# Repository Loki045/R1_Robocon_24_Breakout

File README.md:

# R1_Robocon_24_Breakout
Breakout and control interface PCB designed for Robocon 2024 R1 robot, supporting Arduino Mega + Host Shield stacking, motor control interfaces, and regulated power distribution from external supply modules.

# Robocon 2024 – R1 Control Breakout PCB

This repository contains the hardware design files for the **R1 Control Breakout PCB** used in the Robocon 2024 robot.

The board was designed to serve as a **stackable control and interface breakout**, enabling easy connection of motors, actuators, and control modules using an **Arduino Mega + Host Shield** stack.

---

## 📌 Robot Task Overview

In Robocon 2024, **Robot 1 (R1)** performed the following operations:

- Navigated across Area 1
- Picked up seedlings
- Placed up to **12 seedlings** into assigned circular positions
- Moved to Area 2
- Threw balls in alternating sequence:
  - Team-colored ball (Red/Blue)
  - Violet ball
  - Repeat sequence
- Threw balls toward Area 3 based on number of successfully placed seedlings

This PCB supported the control and actuator interfacing required to perform these tasks.

---

## ⚙️ Board Overview

The R1 PCB was designed as a **centralized control breakout board**, allowing:

- Direct mounting of **Arduino Mega**
- Stacking of **USB Host Shield**
- Organized connection of motors and actuators
- Easy access to multiple communication pins
- Distribution of regulated voltages received from an **external power distribution board**

This modular approach simplified robot wiring and improved system maintainability.

---

## 🔧 Key Features

- Arduino Mega compatible stacking layout
- USB Host Shield support (for controller interface)
- 4 PWM motor connectors for locomotion control
- Servo motor connectors
- Stepper motor connectors
- BLDC motor interface connectors
- Kill switch interface
- External indicating lamp connectors
- Extra UART headers
- Additional GPIO expansion pins
- LED power/status indicators
- Decoupling capacitors for stable operation

---

## 🔌 Power Interface

Regulated voltages were supplied from an **external power distribution board**.

### Input Power (via Screw Terminals):

- 12V Input
- 7.4V Input
- 5V Input

### On-board Power Headers:

- 7.4V Output Headers
- 5V Output Headers
- GND Headers

These headers enabled clean routing of regulated voltages to connected modules.

---

## 🎮 Motor & Actuator Interfaces

### Locomotion Control:

- 4 PWM output connectors for Cytron Smart Drive Mdds30 Dual 30A motor driver

### Actuator Support:

- Multiple Servo connectors
- Stepper motor connectors
- BLDC motor interface connectors

These supported the mechanisms required for seedling placement and ball throwing operations.

---

## 🧩 Additional Interfaces

- Kill Switch Connector
- External Indicator Lamp Connectors
- Extra UART Communication Headers
- General-Purpose GPIO Expansion Pins
- LED Indicators for Power/Status Monitoring

---

## 🧰 Hardware Stack

Designed to support:

- Arduino Mega 2560 (Main Controller)
- USB Host Shield
- Redgear Controller (via Host Shield)

This stack allowed wireless/manual control of the robot.

---

## 📂 Repository Contents

R1_PCB_2024-25_VRC/

    ├── PCB Layout File
    ├── Project File
    ├── Schematic File 
Images/

    ├── Top Layer View  
    ├── Bottom Layer View  
    ├── 3D View  
      
.gitignore

README.md

---

## 🛠 Tools Used

- KiCad — Schematic and PCB Design
- Arduino IDE — Firmware Development

---

## 🎯 Application

This PCB was used in the **Robocon 2024 R1 robot**, providing structured connectivity for locomotion motors, actuators, and control interfaces required for seedling placement and ball-throwing operations.

---

## 👨‍💻 Contribution

Developed as part of the Robocon 2024 electronics system, contributing to hardware layout planning, connector design, and system-level integration for robot subsystems.

---

## 📸 PCB Images

- Schematic

- F.Cu Layer View

- B.Cu Layer View

- 3D View

---

## 📎 Design Intent

This board was designed to reduce wiring complexity, improve modularity, and enable rapid maintenance during robot testing and competition.

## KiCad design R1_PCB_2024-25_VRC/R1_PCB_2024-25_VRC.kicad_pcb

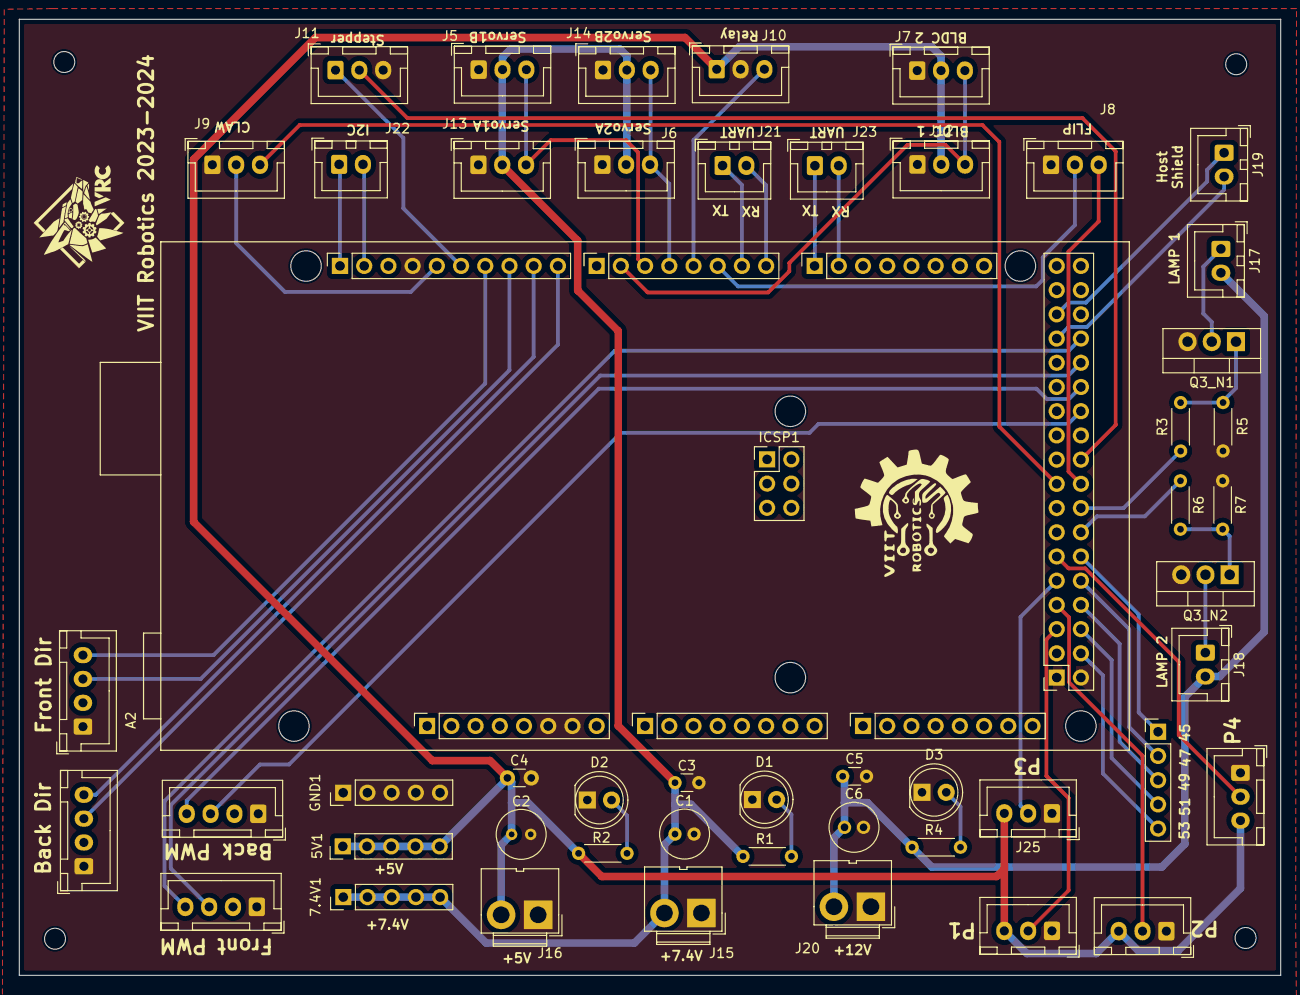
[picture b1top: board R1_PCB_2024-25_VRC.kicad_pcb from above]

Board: 2 copper layers, 132.3 x 100.3 mm, 64 parts (1 on the bottom side), 48 nets.

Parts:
5V1, 7.4V1: Conn_01x05; PinHeader_1x05_P2.54mm_Vertical
., .#2: .; logo
A2: ARDUINO_MEGA_2560_REV3_A000067; ARDUINO_ARDUINO_MEGA_2560_REV3_A000067
C1: 10 mf; C_Radial_D5.0mm_H7.0mm_P2.00mm
C2, C6: 100 nf; C_Radial_D5.0mm_H7.0mm_P2.00mm
C3, C4, C5: 0.1uF; C_Disc_D3.0mm_W1.6mm_P2.50mm
D1, D2, D3: LED; LED_D5.0mm
DIR1: Conn_01x05; PinHeader_1x05_P2.54mm_Vertical
GND1: Conn_01x05; PinHeader_1x05_P2.54mm_Vertical
H1, H2, H3, H4: MountingHole; MountingHole_2.2mm_M2
ICSP1: Conn_02x03_Odd_Even; PinHeader_2x03_P2.54mm_Vertical
J1, J2#2: FRONT; JST_XH_B4B-XH-A_1x04_P2.50mm_Vertical
J1#2: Power; PinSocket_1x08_P2.54mm_Vertical
J2: PWM; PinSocket_1x10_P2.54mm_Vertical
J3, J4#2: BACK; JST_XH_B4B-XH-A_1x04_P2.50mm_Vertical
J3#2, J5: Analog; PinSocket_1x08_P2.54mm_Vertical
J4: PWM; PinSocket_1x08_P2.54mm_Vertical
J5#2, J6#2, J7#2, J8, J9, J10, J11, J12, J13, J14, J24, J25, J26, J27: Conn_01x03; JST_XH_B3B-XH-A_1x03_P2.50mm_Vertical
J6: Communication; PinSocket_1x08_P2.54mm_Vertical
J7: Digital; PinSocket_2x18_P2.54mm_Vertical
J15, J16, J20: Conn_01x02; JWT_A3963_1x02_P3.96mm_Vertical
J17, J18, J19, J21, J22, J23: Conn_01x02; JST_XH_B2B-XH-A_1x02_P2.50mm_Vertical
Q3_N1, Q3_N2: IRF3205; TO-220-3_Vertical
R1, R4: 360; R_Axial_DIN0204_L3.6mm_D1.6mm_P5.08mm_Horizontal
R2: 220; R_Axial_DIN0204_L3.6mm_D1.6mm_P5.08mm_Horizontal
R3, R5, R6, R7: R; R_Axial_DIN0204_L3.6mm_D1.6mm_P5.08mm_Horizontal

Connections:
45: A2.45, DIR1.1, J7.12
47: A2.47, DIR1.2, J7.10
49: A2.49, DIR1.3, J7.8
51: A2.51, DIR1.4, J7.6
53: A2.53, DIR1.5, J7.4
+5V: 5V1.1, 5V1.2, 5V1.3, 5V1.4, 5V1.5, C2.1, C4.1, J7.35, J7.36, J7#2.2, J10.1, J12.2, J16.2, J24.3, J25.3, J26.3, J27.3, R2.2
+7.4V: 7.4V1.1, 7.4V1.2, 7.4V1.3, 7.4V1.4, 7.4V1.5, C1.1, C3.1, J5#2.2, J6#2.2, J13.2, J14.2, J15.2, R1.2
+12V: C5.1, C6.1, J17.2, J18.2, J20.2, R4.2
BL_AN1: A2.8, J2.10, J3.3
BL_IN1: A2.33, J4#2.3, J7.21
BR_AN2: A2.9, J2.9, J3.4
BR_IN2: A2.31, J4#2.4, J7.23
CLAW_DIR: A2.38, J7.17, J9.3
CLAW_PWM: A2.13, J2.5, J9.2
ESC_PWM: A2.6, J4.2, J7#2.3, J12.3
FLIP_DIR: A2.39, J7.18, J8.3
FLIP_PWM: A2.2, J4.6, J8.2
FL_AN1: A2.10, J1.3, J2.8
FL_IN1: A2.29, J2#2.3, J7.25
FR_AN2: A2.11, J1.4, J2.7
FR_IN2: A2.27, J2#2.4, J7.27
GND: A2.GND1, A2.GND2, A2.GND3, A2.GND4, A2.GND5, C1.2, C2.2, C3.2, C4.2, C5.2, C6.2, D1.1 (K), D2.1 (K), D3.1 (K), GND1.1, GND1.2, GND1.3, GND1.4, GND1.5, J1.1, J1#2.6, J1#2.7, J2.4, J2#2.1, J3.1, J4#2.1, J5#2.1, J6#2.1, J7.1, J7.2, J7#2.1, J8.1, J9.1, J10.2, J11.3, J12.1, J13.1, J14.1, J15.1, J16.1, J20.1, J24.1, J25.1, J26.1, J27.1, Q3_N1.3 (S), Q3_N2.3 (S), R5.1, R7.1
INT: A2.26, J7.29, J19.2
LED_DIR1: A2.41, J7.16, R3.1
LED_DIR2: A2.43, J7.14, R6.1
unnamed: D1.2 (A), R1.1
unnamed: D2.2 (A), R2.1
unnamed: D3.2 (A), R4.1
unnamed: J17.1, Q3_N1.2 (D)
unnamed: J18.1, Q3_N2.2 (D)
unnamed: Q3_N1.1 (G), R3.2, R5.2
unnamed: Q3_N2.1 (G), R6.2, R7.2
P1: A2.50, J7.5, J24.2
P2: A2.48, J7.7, J26.2
P3: A2.46, J7.9, J25.2
P4: A2.44, J7.11, J27.2
RELAY_IN: A2.3, J4.5, J10.3
RX0: A2.0, J4.8, J21.2
RX3: A2.15, J6.2, J23.2
SCL: A2.SCL, J2.1, J6.8, J22.1
SDA: A2.SDA, J2.2, J6.7, J22.2
SS: A2.24, J7.31, J19.1
STEPPER_DIR: A2.37, J7.20, J11.2
STEPPER_PULSE: A2.12, J2.6, J11.1
TX0: A2.1, J4.7, J21.1
TX3: A2.14, J6.1, J23.1
~SERVO1: A2.5, J4.3, J5#2.3, J13.3
~SERVO2: A2.4, J4.4, J6#2.3, J14.3

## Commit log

2026-04-18 R1 Breakout 2024 Kicad Project setup
2026-04-18 Add PCB images
